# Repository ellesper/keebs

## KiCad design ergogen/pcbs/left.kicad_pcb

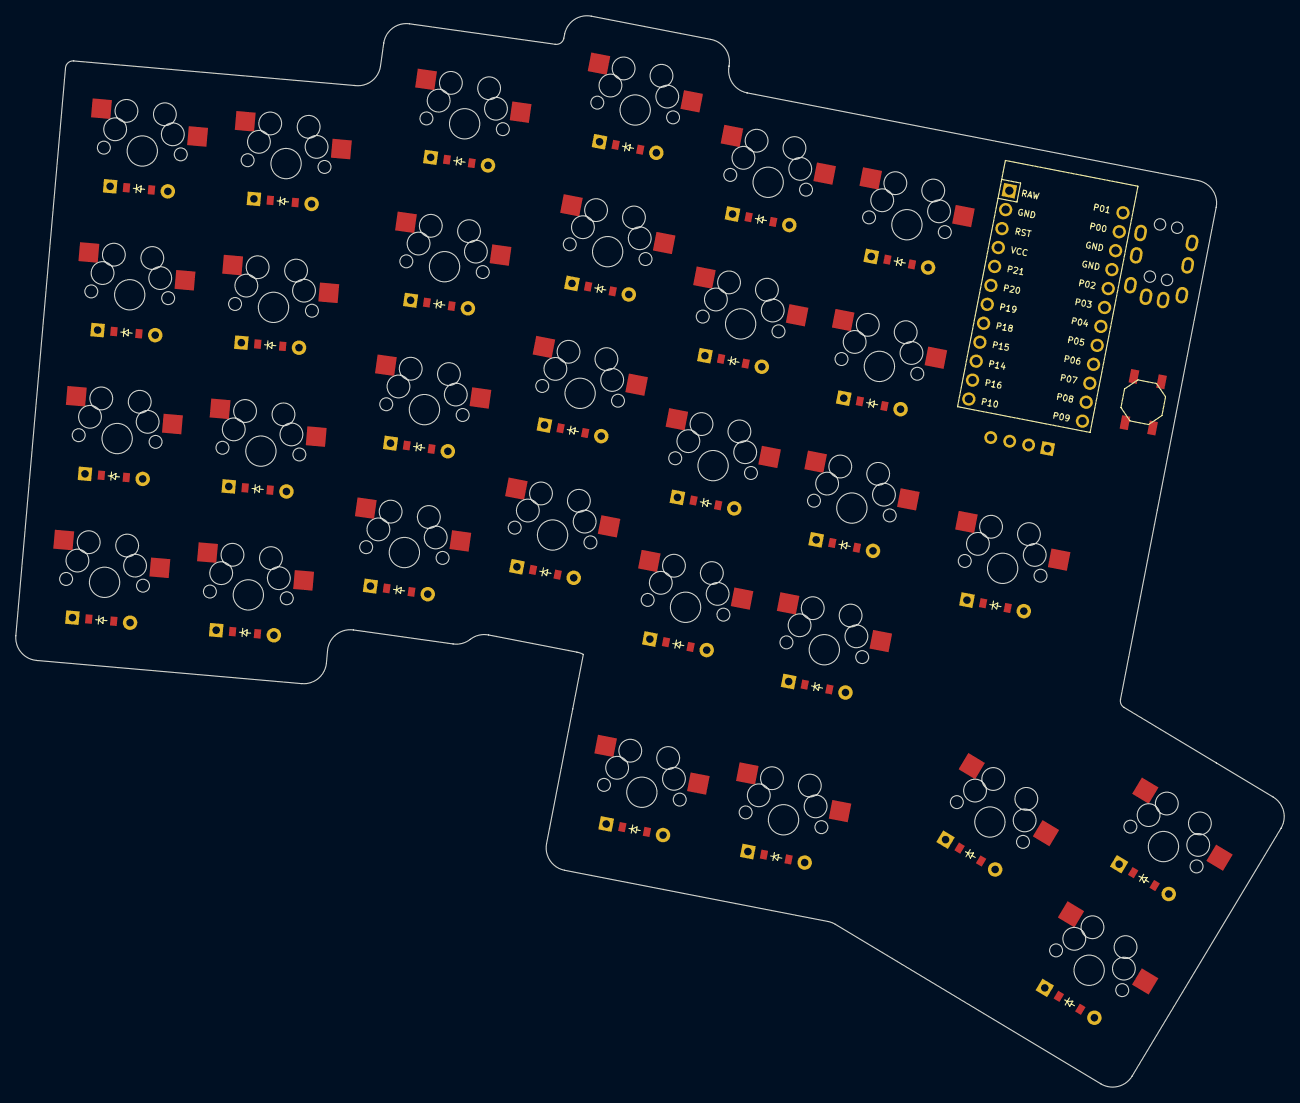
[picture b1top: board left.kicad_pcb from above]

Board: 2 copper layers, 167.0 x 141.0 mm, 64 parts (0 on the bottom side), 49 nets, no tracks yet.

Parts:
B1: SW_TACT_ALPS_SKQGABE010
D1, D2, D3, D4, D5, D6, D7, D8, D9, D10, D11, D12, D13, D14, D15, D16, D17, D18, D19, D20, D21, D22, D23, D24, D25, D26, D27, D28, D29, D30: ComboDiode
MCU1: ProMicro
OLED1: OLED; OLED_headers
S1, S2, S3, S4, S5, S6, S7, S8, S9, S10, S11, S12, S13, S14, S15, S16, S17, S18, S19, S20, S21, S22, S23, S24, S25, S26, S27, S28, S29, S30: MX
TRRS1: TRRS-PJ-320A-dual

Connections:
GND: B1.1, MCU1.2, MCU1.15, MCU1.16, OLED1.1, TRRS1.3
P0: MCU1.14, TRRS1.4
P2: MCU1.17, OLED1.4
P3: MCU1.18, OLED1.3
P4: D4.1, D8.1, D12.1, D16.1, D20.1, D24.1, MCU1.19
P5: D3.1, D7.1, D11.1, D15.1, D19.1, D23.1, MCU1.20
P6: D2.1, D6.1, D10.1, D14.1, D18.1, D22.1, MCU1.21
P7: D1.1, D5.1, D9.1, D13.1, D17.1, D21.1, D25.1, MCU1.22
P8: D30.1, MCU1.23
P9: D26.1, D27.1, D28.1, D29.1, MCU1.24
P14: MCU1.10, S21.1, S22.1, S23.1, S24.1, S28.1
P15: MCU1.9, S17.1, S18.1, S19.1, S20.1, S27.1
P16: MCU1.11, S25.1, S29.1, S30.1
P18: MCU1.8, S13.1, S14.1, S15.1, S16.1, S26.1
P19: MCU1.7, S9.1, S10.1, S11.1, S12.1
P20: MCU1.6, S5.1, S6.1, S7.1, S8.1
P21: MCU1.5, S1.1, S2.1, S3.1, S4.1
RST: B1.2, MCU1.3
VCC: MCU1.4, OLED1.2, TRRS1.2
far_thumb: D30.2, S30.2
far_thumb2: D29.2, S29.2
home_thumb2: D28.2, S28.2
index_bottom: D17.2, S17.2
index_home: D18.2, S18.2
index_top: D19.2, S19.2
index_upper: D20.2, S20.2
inner2_bottom: D25.2, S25.2
inner_bottom: D21.2, S21.2
inner_home: D22.2, S22.2
inner_top: D23.2, S23.2
inner_upper: D24.2, S24.2
middle_bottom: D13.2, S13.2
middle_home: D14.2, S14.2
middle_top: D15.2, S15.2
middle_upper: D16.2, S16.2
near_thumb2: D27.2, S27.2
nearer_thumb2: D26.2, S26.2
pinky2_bottom: D1.2, S1.2
pinky2_home: D2.2, S2.2
pinky2_top: D3.2, S3.2
pinky2_upper: D4.2, S4.2
pinky_bottom: D5.2, S5.2
pinky_home: D6.2, S6.2
pinky_top: D7.2, S7.2
pinky_upper: D8.2, S8.2
ring_bottom: D9.2, S9.2
ring_home: D10.2, S10.2
ring_top: D11.2, S11.2
ring_upper: D12.2, S12.2

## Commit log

2024-09-24 first commit, rough project
2024-09-25 decided to go reversible pcb route, removed right side and added reversible components to left side
